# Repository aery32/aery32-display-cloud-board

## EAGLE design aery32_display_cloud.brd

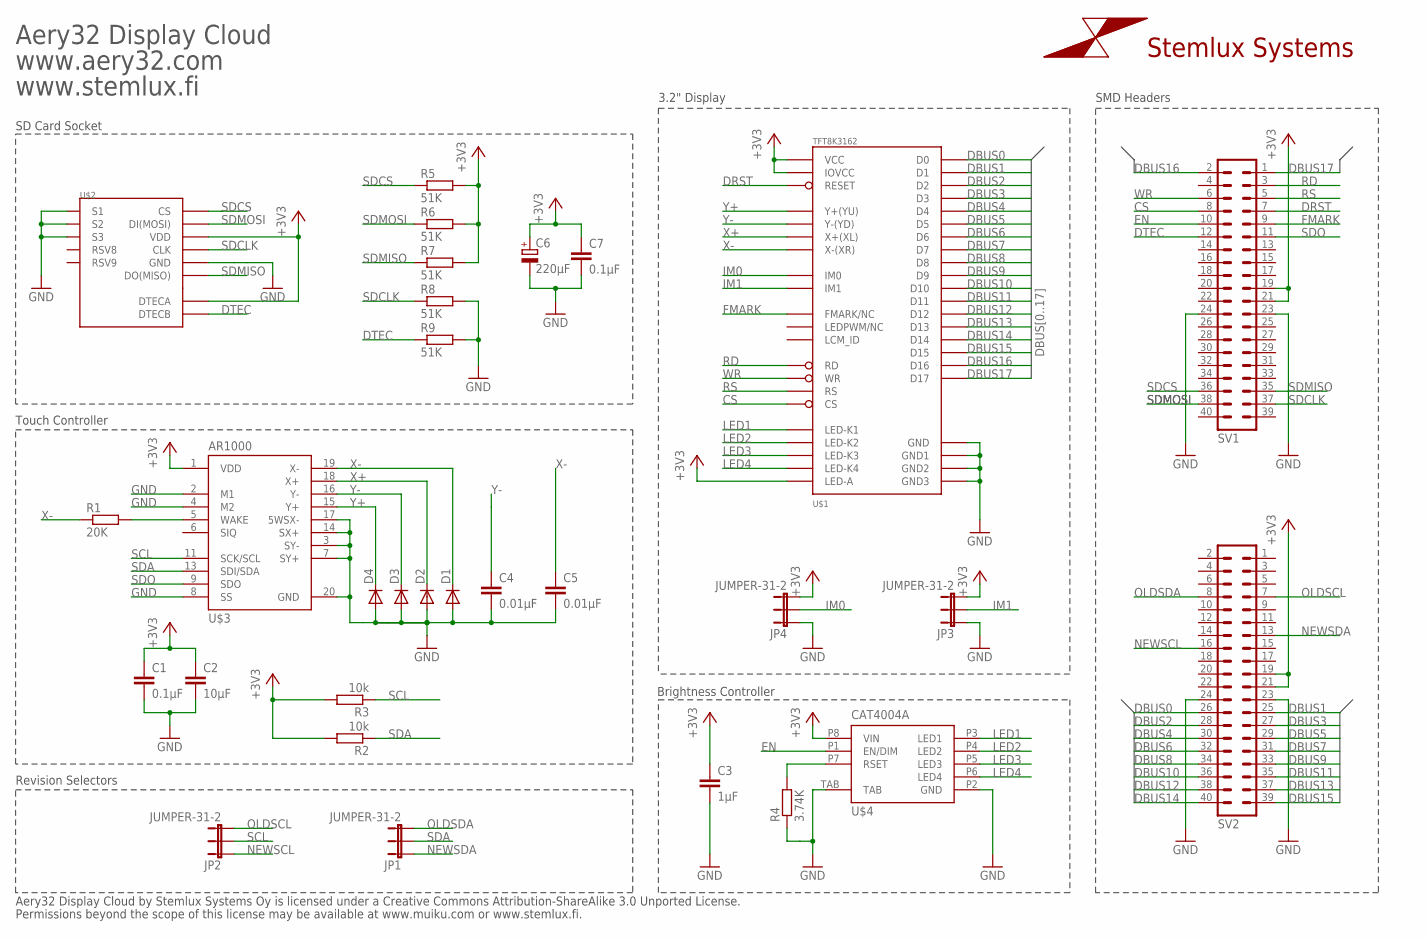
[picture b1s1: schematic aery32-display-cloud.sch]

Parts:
C1, C7: 0.1µF; C0402
C2: 10µF; C0805
C3: 1µF; C0402
C4, C5: 0.01µF; C0402
C6: 220µF; SMC_B
D1, D2, D3, D4: DIODESOD; SOD-323
JP1, JP2, JP3, JP4: JUMPER-31-2; SJ_3_PASTE1&2
R1: 20K; R0402
R2, R3: 10k; R0402
R4: 3.74K; R0402
R5, R6, R7, R8, R9: 51K; R0402
SV1, SV2: MA20-2PEG; MA20-2_SMD
U$1: TFT8K3162
U$2: MICROSD_SOCKETBT; DM3BT_PUSH-PUSH_USD_SOCKET
U$3: AR1000; SSOP20
U$4: CAT4004A; UDFN-8,2X2
U$7: LOGOSS; LOGO_SILK_SMALL

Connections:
+3V3: C1.1, C2.1, C3.1, C6.+, C7.1, JP3.3, JP4.3, R2.2, R3.2, R5.2, R6.2, R7.2, SV1.19, SV1.21, SV2.19, SV2.21, U$1.P$36 (IOVCC), U$1.P$37 (VCC), U$1.P$43 (LED-A), U$2.#4(VDD) (VDD), U$2.DETECTA (DTECA), U$3.1 (VDD), U$4.P8 (VIN)
CS: SV1.8, U$1.P$34 (CS)
DBUS0: SV2.26, U$1.P$30 (D0)
DBUS1: SV2.25, U$1.P$29 (D1)
DBUS2: SV2.28, U$1.P$28 (D2)
DBUS3: SV2.27, U$1.P$27 (D3)
DBUS4: SV2.30, U$1.P$26 (D4)
DBUS5: SV2.29, U$1.P$25 (D5)
DBUS6: SV2.32, U$1.P$24 (D6)
DBUS7: SV2.31, U$1.P$23 (D7)
DBUS8: SV2.34, U$1.P$22 (D8)
DBUS9: SV2.33, U$1.P$21 (D9)
DBUS10: SV2.36, U$1.P$20 (D10)
DBUS11: SV2.35, U$1.P$19 (D11)
DBUS12: SV2.38, U$1.P$18 (D12)
DBUS13: SV2.37, U$1.P$17 (D13)
DBUS14: SV2.40, U$1.P$16 (D14)
DBUS15: SV2.39, U$1.P$15 (D15)
DBUS16: SV1.2, U$1.P$14 (D16)
DBUS17: SV1.1, U$1.P$13 (D17)
DRST: SV1.7, U$1.P$12 (RESET)
DTEC: R9.1, SV1.12, U$2.DETECTB (DTECB)
EN: SV1.10, U$4.P1 (EN/DIM)
FMARK: SV1.9, U$1.P$9 (FMARK/NC)
GND: C1.2, C2.2, C3.2, C4.2, C5.2, C6.-, C7.2, D1.2 (A), D2.2 (A), D3.2 (A), D4.2 (A), JP3.1, JP4.1, R4.1, R8.2, R9.2, SV1.23, SV1.24, SV2.23, SV2.24, U$1.P$1 (GND), U$1.P$6 (GND1), U$1.P$35 (GND2), U$1.P$44 (GND3), U$2.#6(VSS) (GND), U$2.SHIELD1 (S1), U$2.SHIELD2 (S2), U$2.SHIELD3 (S3), U$3.2 (M1), U$3.3 (SY-), U$3.4 (M2), U$3.7 (SY+), U$3.8 (SS), U$3.14 (SX+), U$3.17 (5WSX-), U$3.20 (GND), U$4.P2 (GND), U$4.TAB
IM0: JP4.2, U$1.P$7 (IM0)
IM1: JP3.2, U$1.P$8 (IM1)
LED1: U$1.P$42 (LED-K1), U$4.P3 (LED1)
LED2: U$1.P$41 (LED-K2), U$4.P4 (LED2)
LED3: U$1.P$40 (LED-K3), U$4.P5 (LED3)
LED4: U$1.P$39 (LED-K4), U$4.P6 (LED4)
unnamed: R4.2, U$4.P7 (RSET)
unnamed: R1.2, U$3.5 (WAKE)
NEWSCL: JP2.1, SV2.16
NEWSDA: JP1.1, SV2.13
OLDSCL: JP2.3, SV2.7
OLDSDA: JP1.3, SV2.8
RD: SV1.3, U$1.P$31 (RD)
RS: SV1.5, U$1.P$33 (RS)
SCL: JP2.2, R3.1, U$3.11 (SCK/SCL)
SDA: JP1.2, R2.1, U$3.13 (SDI/SDA)
SDCLK: R8.1, SV1.37, U$2.#5(CLK) (CLK)
SDCS: R5.1, SV1.36, U$2.#1(DAT3_OR_CS) (CS)
SDMISO: R7.1, SV1.35, U$2.#7(DAT0_OR_DO) (DO(MISO))
SDMOSI: R6.1, SV1.38, U$2.2#(CMD_OR_DI) (DI(MOSI))
SDO: SV1.11, U$3.9 (SDO)
WR: SV1.6, U$1.P$32 (WR)
X+: D2.1 (C), U$1.P$3 (X+(XL)), U$3.18 (X+)
X-: C5.1, D1.1 (C), R1.1, U$1.P$5 (X-(XR)), U$3.19 (X-)
Y+: D4.1 (C), U$1.P$2 (Y+(YU)), U$3.15 (Y+)
Y-: C4.1, D3.1 (C), U$1.P$4 (Y-(YD)), U$3.16 (Y-)

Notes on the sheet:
www.aery32.com
Aery32 Display Cloud
Aery32 Display Cloud by Stemlux Systems Oy is licensed under a Creative Commons Attribution-ShareAlike 3.0 Unported License.
Permissions beyond the scope of this license may be available at www.muiku.com or www.stemlux.fi.
www.stemlux.fi
SD Card Socket
Touch Controller
Revision Selectors
Brightness Controller
3.2" Display
SMD Headers

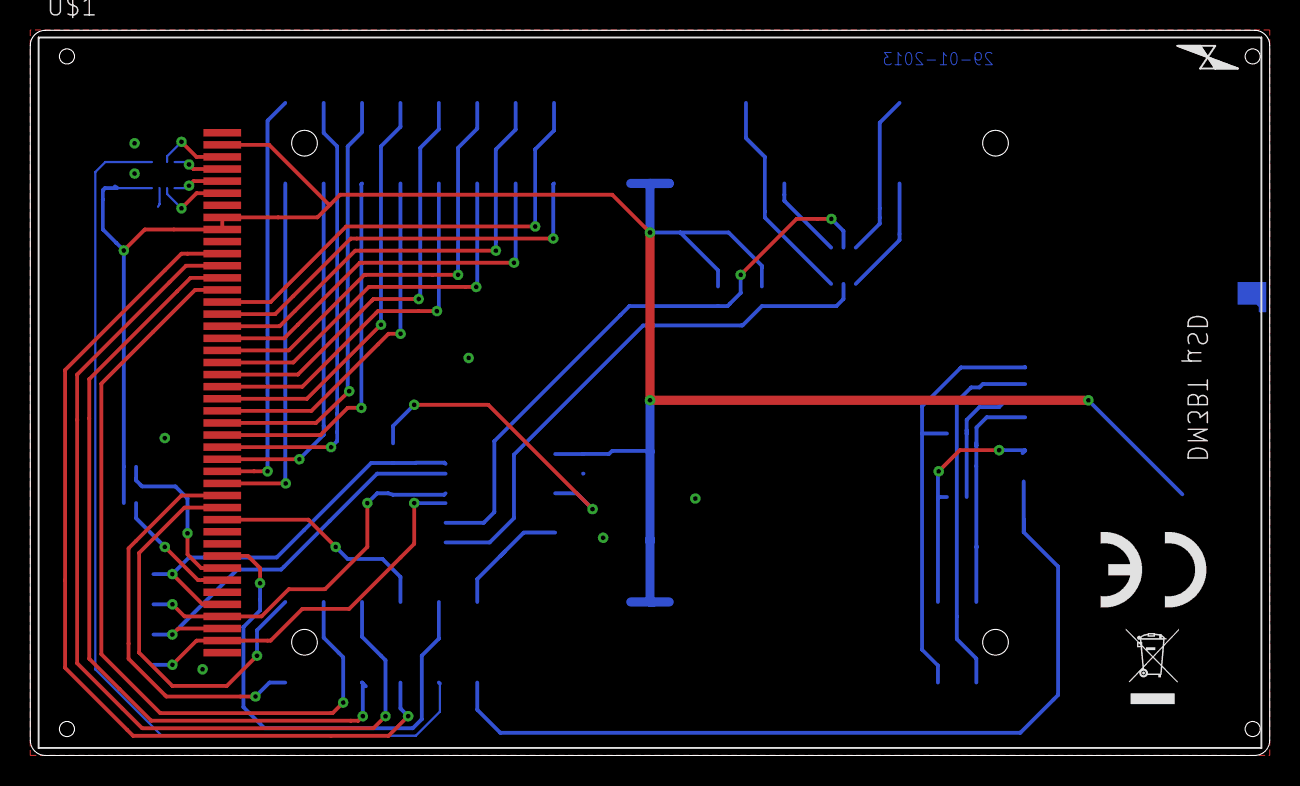
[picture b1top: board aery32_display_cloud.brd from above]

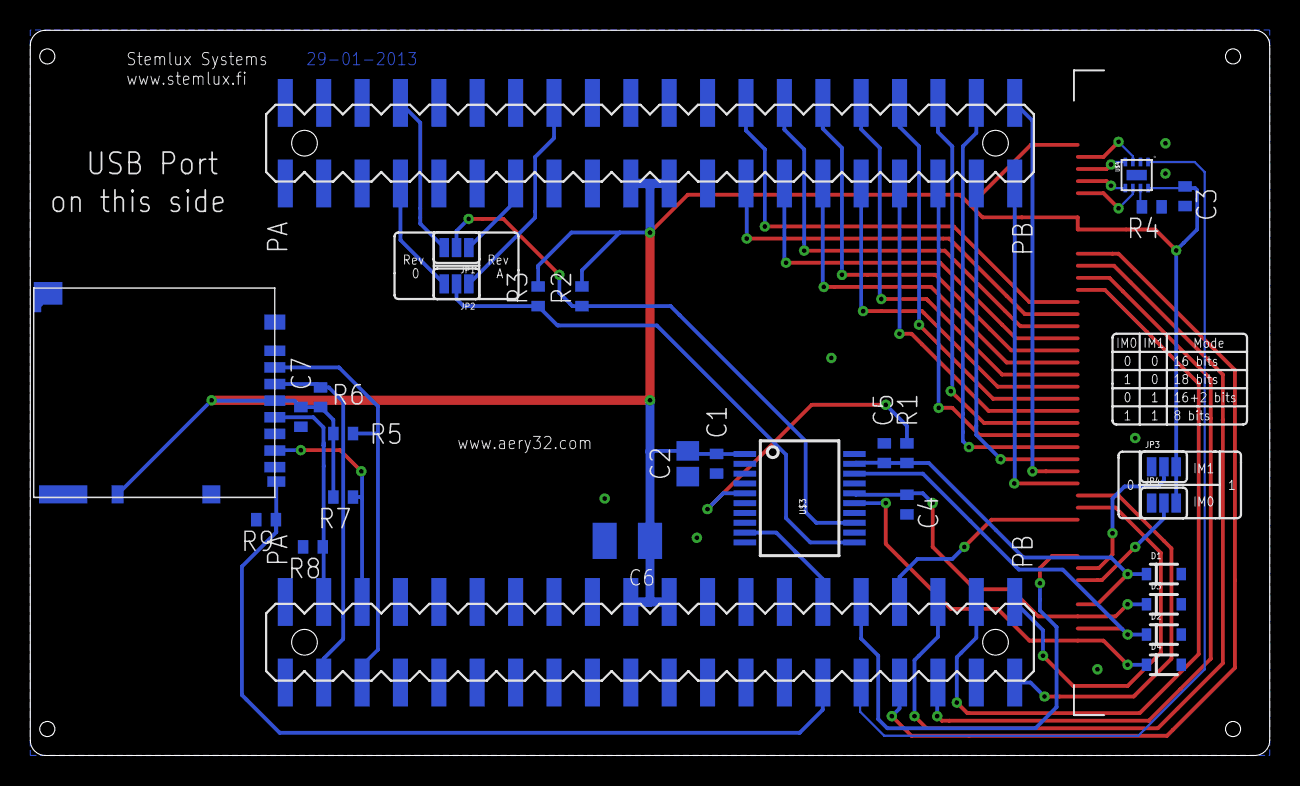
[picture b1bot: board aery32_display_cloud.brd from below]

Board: 2 copper layers, 82.0 x 48.0 mm, 33 parts (33 on the bottom side), 51 nets.

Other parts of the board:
U$5: CE/5MM
U$6: WEEE/5MM

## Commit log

2013-04-14 Add schematics in pdf format

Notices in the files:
parts and their libraries:
SparkFun-DiscreteSemi: Licensing: CC v3.0 Share-Alike You are welcome to use this library for commercial purposes.
